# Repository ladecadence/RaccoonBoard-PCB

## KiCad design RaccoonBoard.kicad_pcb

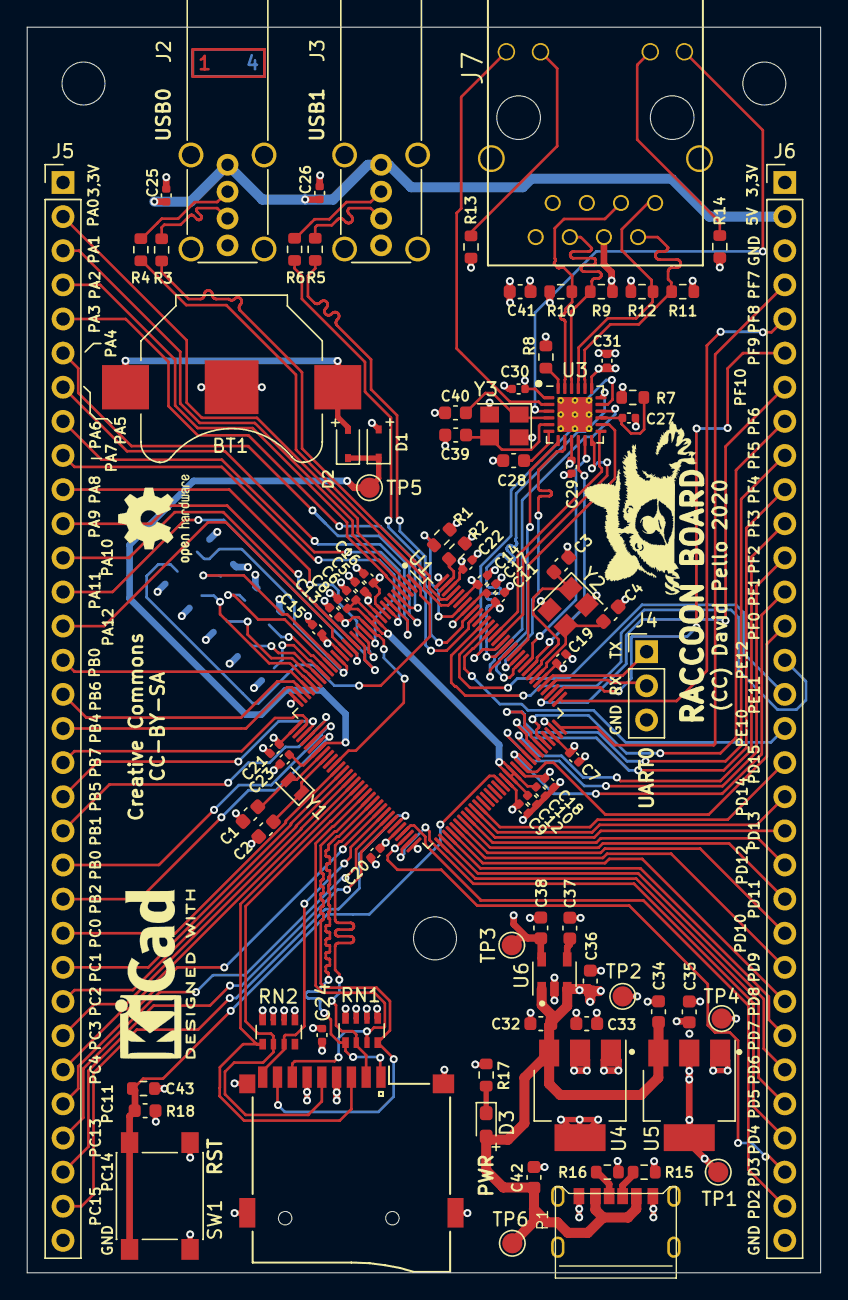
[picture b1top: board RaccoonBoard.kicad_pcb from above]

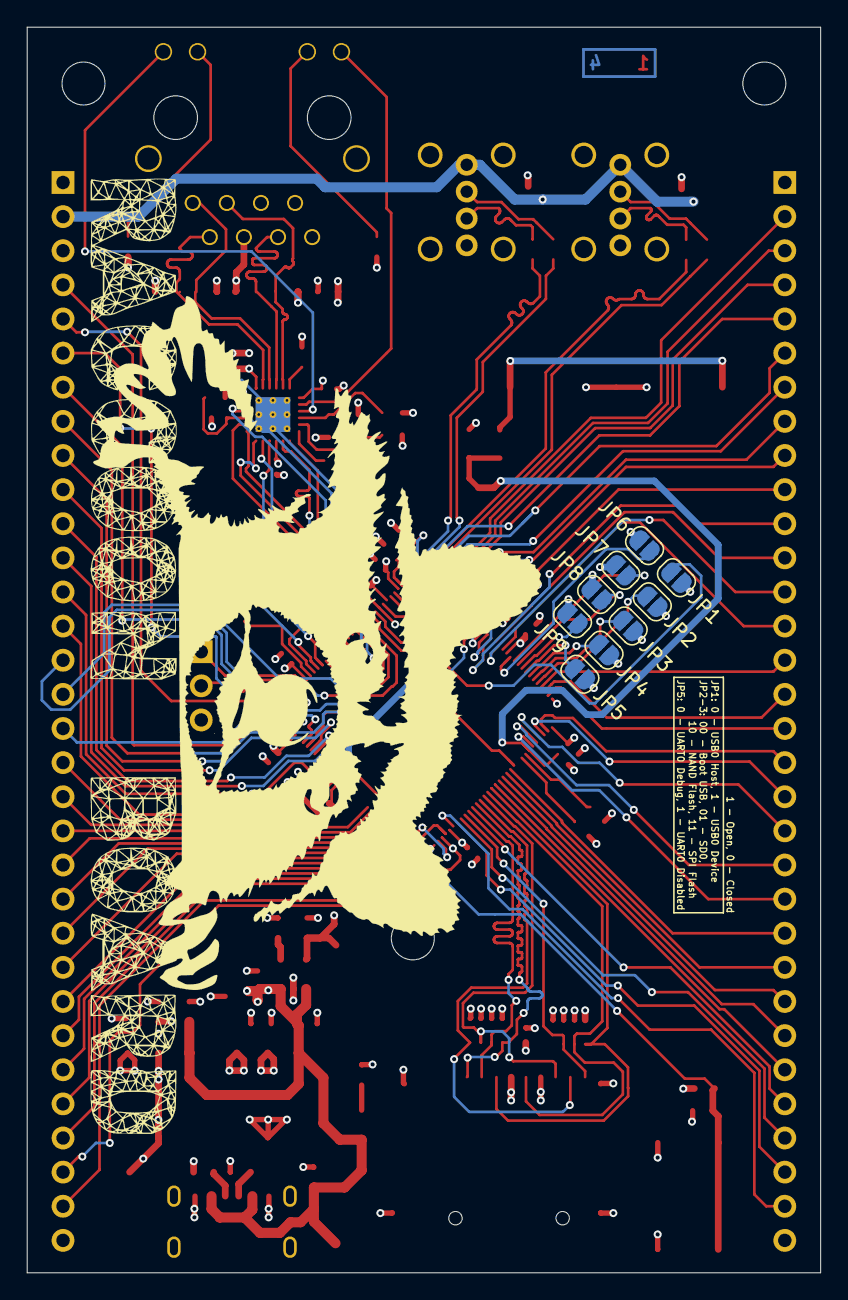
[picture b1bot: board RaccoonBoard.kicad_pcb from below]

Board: 4 copper layers, 59.1 x 92.7 mm, 99 parts (9 on the bottom side), 125 nets.

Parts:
BT1: 3V; Keystone_3000_1x12mm-CoinCell
C1, C2, C3, C4, C39, C40: C; C_0603_1608Metric
C5, C6, C7, C8, C9, C10, C11, C12, C13, C14, C15, C16, C17, C18, C19, C20, C21, C22, C23, C24, C25, C26, C27, C29, C30, C31: 100n; C_0402_1005Metric
C28, C32, C33, C34, C35, C36, C38, C42, C43: 1u; C_0603_1608Metric
C37, C41: 10n; C_0603_1608Metric
D1, D2: BAT43WS; D_SOD-323
D3: PWR; LED_0603_1608Metric_Pad1.05x0.95mm_HandSolder
J1: BOOT SD; Conn_uSDcard
J2, J3: USB_A; USB_A_Vertical
J4: UART0; PinHeader_1x03_P2.54mm_Vertical
J5: IO1; PinHeader_1x32_P2.54mm_Vertical
J6: IO2; PinHeader_1x32_P2.54mm_Vertical
J7: HR911105A; HR911105a
JP1: USB0ID; SolderJumper-2_P1.3mm_Open_RoundedPad1.0x1.5mm
JP2: PG0; SolderJumper-2_P1.3mm_Open_RoundedPad1.0x1.5mm
JP3: PG1; SolderJumper-2_P1.3mm_Open_RoundedPad1.0x1.5mm
JP4: PG3; SolderJumper-2_P1.3mm_Open_RoundedPad1.0x1.5mm
JP5: PG5; SolderJumper-2_P1.3mm_Open_RoundedPad1.0x1.5mm
JP6: PG9; SolderJumper-2_P1.3mm_Open_RoundedPad1.0x1.5mm
JP7: PG8; SolderJumper-2_P1.3mm_Open_RoundedPad1.0x1.5mm
JP8: PG7; SolderJumper-2_P1.3mm_Open_RoundedPad1.0x1.5mm
JP9: PG6; SolderJumper-2_P1.3mm_Open_RoundedPad1.0x1.5mm
P1: USB PWR; TYPE-C-31-M-17
R1, R2, R8: 12K1; R_0603_1608Metric
R3, R4, R5, R6: 4R7; R_0603_1608Metric
R7: 10K; R_0603_1608Metric
R9, R10, R11, R12: 49.9; R_0603_1608Metric
R13, R14, R17: 220; R_0603_1608Metric
R15, R16: 5K1; R_0603_1608Metric
R18: 100K; R_0603_1608Metric
RN1, RN2: 10K; R_Array_Convex_4x0603
SW1: RST; SW_Push_1P1T_NO_6x6mm_H9.5mm
TP1: 1.2; TestPoint_Pad_D1.5mm
TP2: 3.3; TestPoint_Pad_D1.5mm
TP3: 1.8; TestPoint_Pad_D1.5mm
TP4: GND; TestPoint_Pad_D1.5mm
TP5: VBATT; TestPoint_Pad_D1.5mm
TP6: VIN; TestPoint_Pad_D1.5mm
U1: NUC980DK61Y; LQFP-128_14x14mm_P0.4mm
U3: LAN8720A; QFN-24-1EP_4x4mm_P0.5mm_EP2.6x2.6mm_ThermalVias
U4: AP1117-33; SOT-223-3_TabPin2
U5: AZ1117-1.2; SOT-223-3_TabPin2
U6: LP2985-1.8; SOT-23-5
Y1: 32K; Crystal_SMD_2012-2Pin_2.0x1.2mm
Y2: 12MHz; Crystal_SMD_3225-4Pin_3.2x2.5mm
Y3: 25MHz; Crystal_SMD_3225-4Pin_3.2x2.5mm

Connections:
+1V2: C5.1, C7.1, C9.1, C11.1, C13.1, C14.1, C35.1, TP1.1, U1.10, U1.13, U1.43, U1.82, U1.94, U1.118, U1.123, U5.2
+1V8: C6.1, C8.1, C10.1, C12.1, C38.1, TP3.1, U1.11, U1.12, U1.83, U1.84, U6.5
+3V3: C15.1, C16.1, C17.1, C18.1, C19.1, C20.1, C21.1, C22.1, C24.1, C29.1, C30.1, C31.1, C33.1, C41.1, D1.2, J1.4, J5.1, J6.1, J7.4, J7.5, R7.1, R9.1, R10.1, R11.1, R12.1, R18.1, RN1.5, RN1.6, RN1.7, RN1.8, RN2.5, RN2.6, RN2.7, RN2.8, TP2.1, U1.9, U1.20, U1.33, U1.60, U1.85, U1.102, U1.121, U1.126, U3.1, U3.9, U3.19, U4.2
+5V: C25.1, C26.1, C32.1, C34.1, C36.1, C42.1, D3.2, J2.1, J3.1, J6.2, P1.A9, P1.B9, TP6.1, U4.3, U5.3, U6.1, U6.3
+BATT: C23.1, D1.1, D2.1, TP5.1, U1.39
/D0+: J2.3, R3.1
/D0-: J2.2, R4.1
/D1+: J3.3, R5.1
/D1-: J3.2, R6.1
ETH_CRSDV: U1.106, U3.11
ETH_LED1: J7.9, U3.3
ETH_LED2: J7.12, U3.2
ETH_MDC: U1.114, U3.13
ETH_MDIO: U1.113, U3.12
ETH_REFCLK: U1.109, U3.14
ETH_RXD0: U1.108, U3.8
ETH_RXD1: U1.107, U3.7
ETH_RXERR: U1.105, U3.10
ETH_RX_N: J7.6, R9.2, U3.22
ETH_RX_P: J7.3, R10.2, U3.23
ETH_TXD0: U1.112, U3.17
ETH_TXD1: U1.111, U3.18
ETH_TXDEN: U1.110, U3.16
ETH_TX_N: J7.2, R11.2, U3.20
ETH_TX_P: J7.1, R12.2, U3.21
GND: BT1.2, C1.2, C2.2, C3.2, C4.2, C5.2, C6.2, C7.2, C8.2, C9.2, C10.2, C11.2, C12.2, C13.2, C14.2, C15.2, C16.2, C17.2, C18.2, C19.2, C20.2, C21.2, C22.2, C23.2, C24.2, C25.2, C26.2, C27.2, C28.2, C29.2, C30.2, C31.2, C32.2, C33.2, C34.2, C35.2, C36.2, C37.2, C38.2, C39.2, C40.2, C41.2, C42.2, C43.2, J1.6, J2.4, J2.5, J3.4, J3.5, J4.3, J5.32, J6.3, J6.32, J7.8, J7.13, J7.14, JP1.1, JP2.1, JP3.1, JP4.1, JP5.1, JP6.2, JP7.2, JP8.2, JP9.2, P1.A12, P1.B12, R1.2, R2.2, R8.2, R13.2, R14.2, R15.2, R16.2, R17.2, SW1.1, TP4.1, U1.32, U1.64, U1.95, U1.128, U3.25, U4.1, U5.1, U6.2, Y2.2, Y2.4, Y3.2, Y3.4
unnamed: BT1.1, D2.2
unnamed: C1.1, U1.40, Y1.2
unnamed: C2.1, U1.41, Y1.1
unnamed: C3.1, U1.104, Y2.1
unnamed: C4.1, U1.103, Y2.3
unnamed: C27.1, R7.2, U3.15
unnamed: C28.1, U3.6
unnamed: C37.1, U6.4
unnamed: C39.1, U3.5, Y3.3
unnamed: C40.1, U3.4, Y3.1
unnamed: D3.1, R17.1
unnamed: J7.10, R14.1
unnamed: J7.11, R13.1
unnamed: JP1.2, U1.1
unnamed: JP2.2, U1.28
unnamed: JP3.2, U1.27
unnamed: JP4.2, U1.26
unnamed: JP5.2, U1.25
unnamed: JP6.1, U1.21
unnamed: JP7.1, U1.22
unnamed: JP8.1, U1.23
unnamed: JP9.1, U1.24
unnamed: P1.A5, R16.1
unnamed: P1.B5, R15.1
unnamed: R1.1, U1.122
unnamed: R2.1, U1.127
unnamed: R8.1, U3.24
PA0: J5.2, U1.2
PA1: J5.3, U1.3
PA2: J5.4, U1.4
PA3: J5.5, U1.5
PA4: J5.6, U1.6
PA5: J5.7, U1.7
PA6: J5.8, U1.8
PA7: J5.9, U1.14
PA8: J5.10, U1.15
PA9: J5.11, U1.16
PA10: J5.12, U1.17
PA11: J5.13, U1.18
PA12: J5.14, U1.19
PB0: J5.15, U1.29
PB1: J5.20, U1.36
PB2: J5.22, U1.38
PB3: J5.21, U1.37
PB4: J5.17, U1.31
PB5: J5.19, U1.35
PB6: J5.16, U1.30
PB7: J5.18, U1.34
PC0: J5.23, U1.44
PC1: J5.24, U1.45
PC2: J5.25, U1.46
PC3: J5.26, U1.47
PC4: J5.27, U1.48
PC11: J5.28, U1.55
PC13: J5.29, U1.57
PC14: J5.30, U1.58
PC15: J5.31, U1.59
PD2: J6.31, U1.61
PD3: J6.30, U1.62
PD4: J6.29, U1.63
PD5: J6.28, U1.65
PD6: J6.27, U1.66
PD7: J6.26, U1.67
PD8: J6.25, U1.68
PD9: J6.24, U1.69
PD10: J6.23, U1.70
PD11: J6.22, U1.71
PD12: J6.21, U1.72
PD13: J6.20, U1.73
PD14: J6.19, U1.74
PD15: J6.18, U1.75
PE10: J6.17, U1.115
PE11: J6.16, U1.116
PE12: J6.15, U1.117
PF0: J6.14, U1.86
PF1: J6.13, U1.87
PF2: J6.12, U1.88
PF3: J6.11, U1.89
PF4: J6.10, U1.90
PF5: J6.9, U1.91
PF6: J6.8, U1.92
PF7: J6.4, U1.96
PF8: J6.5, U1.97
PF9: J6.6, U1.98
PF10: J6.7, U1.99
SD0CLK: J1.5, RN2.2, U1.50
SD0CMD: J1.3, RN2.1, U1.49
SD0DAT0: J1.7, RN1.3, U1.51
SD0DAT1: J1.8, RN1.4, U1.52
SD0DAT2: J1.1, RN1.1, U1.53
SD0DAT3: J1.2, RN1.2, U1.54
SD0DETECT: J1.9, RN2.3, U1.56
UART0RX: J4.2, U1.100
UART0TX: J4.1, U1.101
USB0D_N: R4.2, U1.124
USB0D_P: R3.2, U1.125
USB1D_N: R6.2, U1.119
USB1D_P: R5.2, U1.120
nRST: C43.1, R18.2, SW1.2, U1.81

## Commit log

2020-12-10 Initial import to github
2020-12-11 Improved USB and ETH routing (matched lengths/skew)
2020-12-11 Updated to lastest KiCAD libraries, improved silkscreens, small fixes to routing
2020-12-12 Added values to XTAL load capacitors
2020-12-12 Moved pin1 mark

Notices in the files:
RaccoonBoard.kicad_pcb:
Creative Commons
CC-BY-SA
